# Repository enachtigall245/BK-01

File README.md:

# BK-01
BattleKeeb-01 Prototyping Files

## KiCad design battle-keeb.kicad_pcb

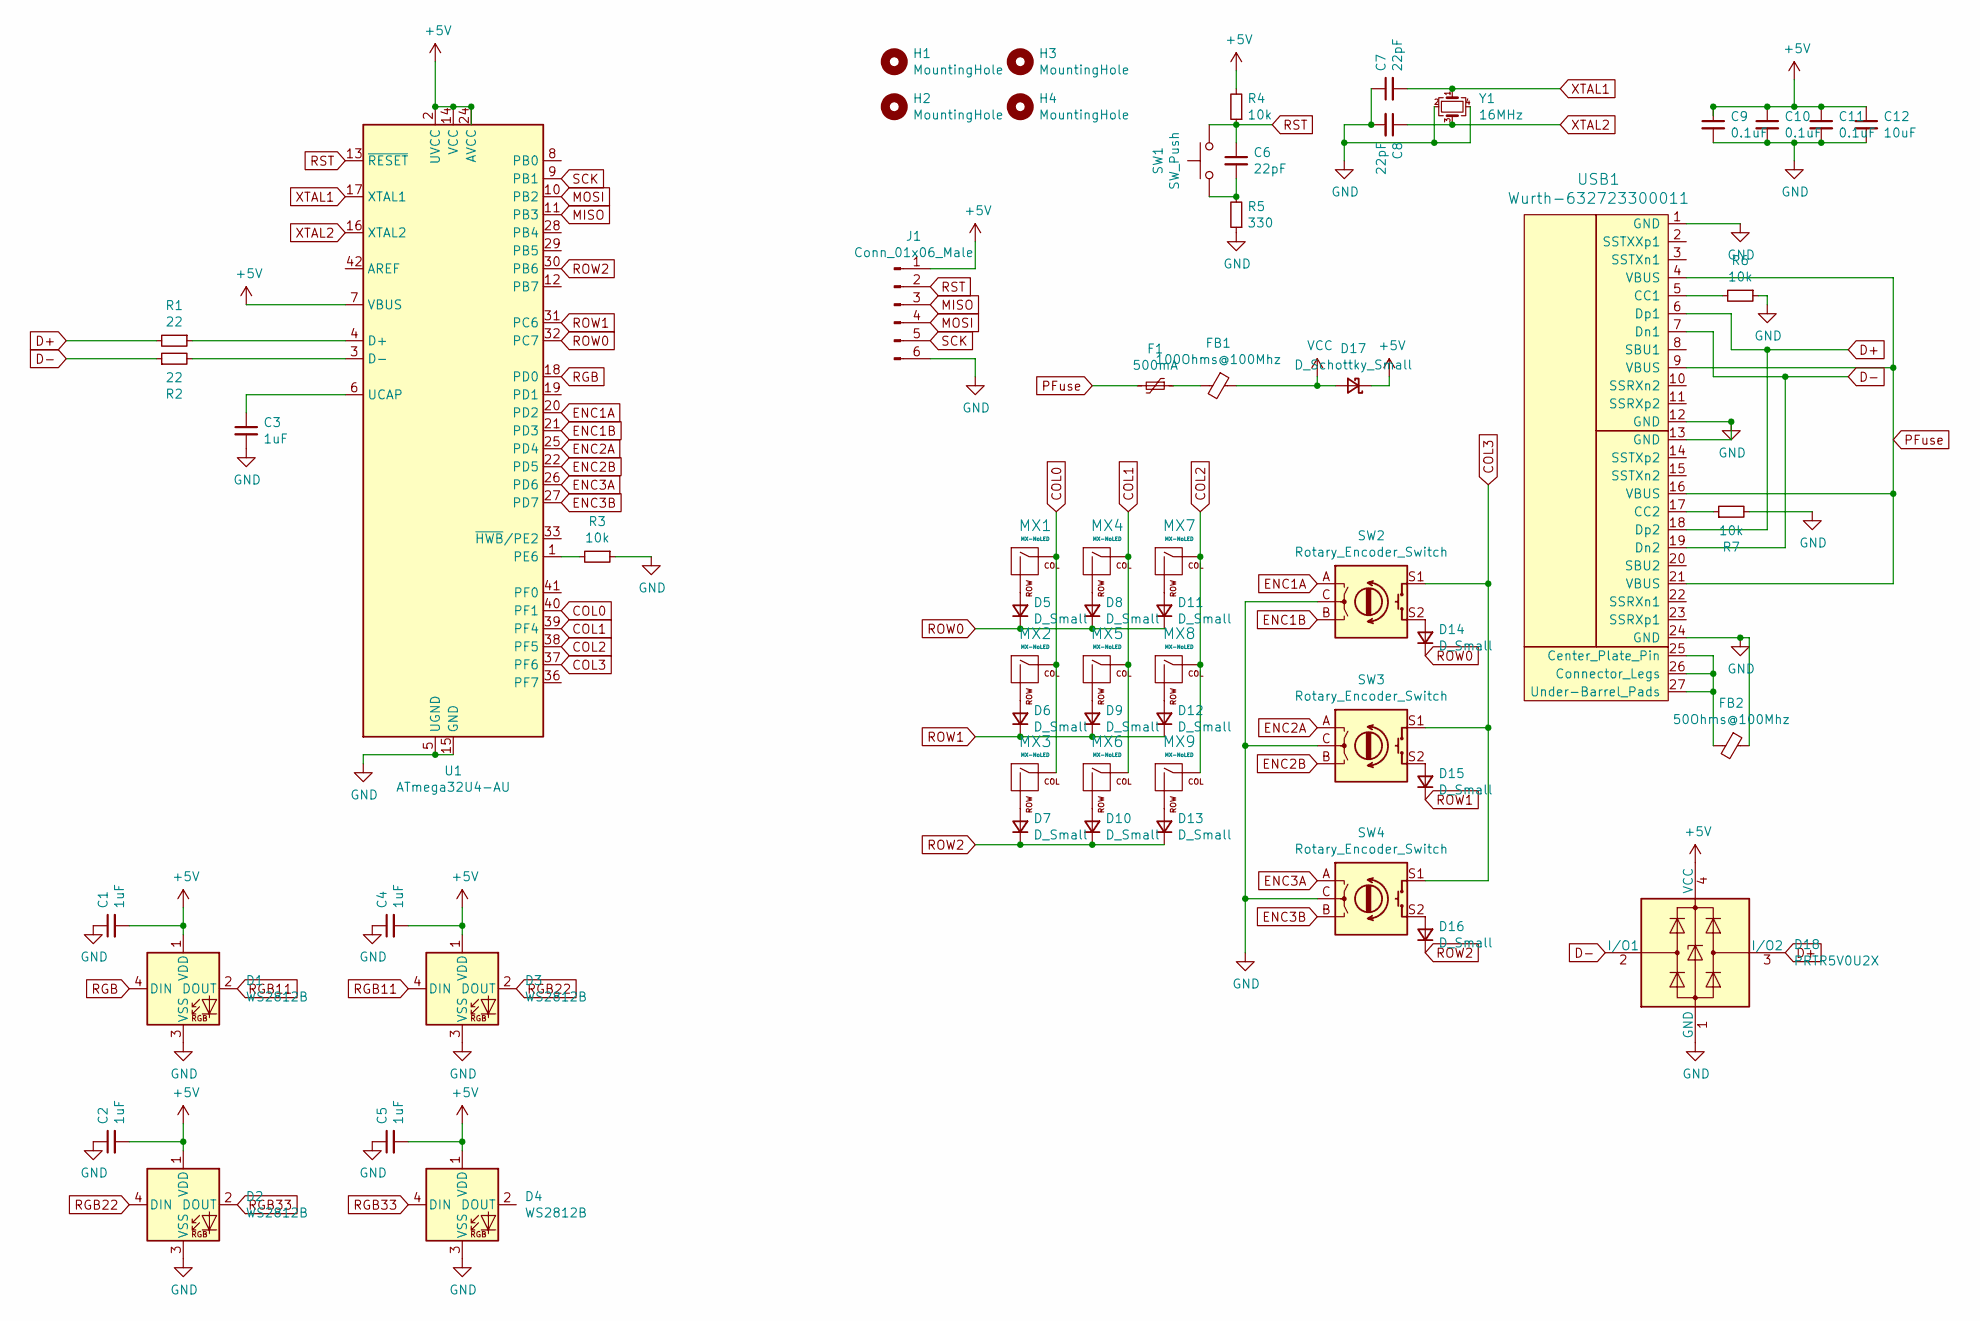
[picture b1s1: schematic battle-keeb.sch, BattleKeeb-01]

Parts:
C1, C2, C3, C4, C5: 1uF; C_0603_1608Metric_Pad1.08x0.95mm_HandSolder
C6, C7, C8: 22pF; C_0603_1608Metric_Pad1.08x0.95mm_HandSolder
C9, C10, C11: 0.1uF; C_0603_1608Metric_Pad1.08x0.95mm_HandSolder
C12: 10uF; C_0603_1608Metric_Pad1.08x0.95mm_HandSolder
D1, D2, D3, D4: WS2812B; LED_WS2812B_PLCC4_5.0x5.0mm_P3.2mm
D5, D6, D7, D8, D9, D10, D11, D12, D13, D14, D15, D16: D_Small; D_SOD-123
D17: D_Schottky_Small; D_SOD-123
D18: PRTR5V0U2X; SOT-143
F1: 500mA; Fuse_1206_3216Metric_Pad1.42x1.75mm_HandSolder
FB1: 100Ohms@100Mhz; R_0603_1608Metric_Pad0.98x0.95mm_HandSolder
FB2: 50Ohms@100Mhz; R_0603_1608Metric_Pad0.98x0.95mm_HandSolder
H1, H2, H3, H4: MountingHole; MountingHole_2.7mm_M2.5_ISO7380_Pad_TopBottom
J1: Conn_01x06_Male; JST_EH_S6B-EH_1x06_P2.50mm_Horizontal
MX1, MX2, MX3, MX4, MX5, MX6, MX7, MX8, MX9: MX-NoLED; MX-1U
R1, R2: 22; R_0603_1608Metric_Pad0.98x0.95mm_HandSolder
R3, R4, R6, R7: 10k; R_0603_1608Metric_Pad0.98x0.95mm_HandSolder
R5: 330; R_0603_1608Metric_Pad0.98x0.95mm_HandSolder
SW1: SW_Push; SKQG-1155865
SW2, SW3, SW4: Rotary_Encoder_Switch; RotaryEncoder_EC11
U1: ATmega32U4-AU; TQFP-44_10x10mm_P0.8mm
USB1: Wurth-632723300011; Wurth-632723300011-HandSoldering
Y1: 16MHz; Crystal_SMD_3225-4Pin_3.2x2.5mm_HandSoldering

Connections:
+5V: C1.2, C2.2, C4.2, C5.2, C9.1, C10.1, C11.1, C12.1, D1.1 (VDD), D2.1 (VDD), D3.1 (VDD), D4.1 (VDD), D17.1 (K), D18.4 (VCC), J1.1, R4.2, U1.2 (UVCC), U1.7 (VBUS), U1.14 (VCC), U1.24 (AVCC), U1.34 (VCC), U1.44 (AVCC)
COL0: MX1.1 (COL), MX2.1 (COL), MX3.1 (COL), U1.40 (PF1)
COL1: MX4.1 (COL), MX5.1 (COL), MX6.1 (COL), U1.39 (PF4)
COL2: MX7.1 (COL), MX8.1 (COL), MX9.1 (COL), U1.38 (PF5)
COL3: SW2.S1, SW3.S1, SW4.S1, U1.37 (PF6)
D+: D18.3 (I/O2), R1.2, USB1.6 (Dp1), USB1.18 (Dp2)
D-: D18.2 (I/O1), R2.1, USB1.7 (Dn1), USB1.19 (Dn2)
ENC1A: SW2.A, U1.20 (PD2)
ENC1B: SW2.B, U1.21 (PD3)
ENC2A: SW3.A, U1.25 (PD4)
ENC2B: SW3.B, U1.22 (PD5)
ENC3A: SW4.A, U1.26 (PD6)
ENC3B: SW4.B, U1.27 (PD7)
GND: C1.1, C2.1, C3.2, C4.1, C5.1, C7.1, C8.2, C9.2, C10.2, C11.2, C12.2, D1.3 (VSS), D2.3 (VSS), D3.3 (VSS), D4.3 (VSS), D18.1 (GND), FB2.1, J1.6, R3.1, R5.1, R6.1, R7.2, SW2.C, SW3.C, SW4.C, U1.5 (UGND), U1.15 (GND), U1.23 (GND), U1.35 (GND), U1.43 (GND), USB1.1 (GND), USB1.12 (GND), USB1.13 (GND), USB1.24 (GND), Y1.2, Y1.4
MISO: J1.3, U1.11 (PB3)
MOSI: J1.4, U1.10 (PB2)
unnamed: C3.1, U1.6 (UCAP)
unnamed: C6.2, R5.2, SW1.1
unnamed: D5.2 (A), MX1.2 (ROW)
unnamed: D6.2 (A), MX2.2 (ROW)
unnamed: D7.2 (A), MX3.2 (ROW)
unnamed: D8.2 (A), MX4.2 (ROW)
unnamed: D9.2 (A), MX5.2 (ROW)
unnamed: D10.2 (A), MX6.2 (ROW)
unnamed: D11.2 (A), MX7.2 (ROW)
unnamed: D12.2 (A), MX8.2 (ROW)
unnamed: D13.2 (A), MX9.2 (ROW)
unnamed: D14.2 (A), SW2.S2
unnamed: D15.2 (A), SW3.S2
unnamed: D16.2 (A), SW4.S2
unnamed: F1.1, FB1.2
unnamed: FB2.2, USB1.25 (Center_Plate_Pin), USB1.26 (Connector_Legs), USB1.27 (Under-Barrel_Pads)
unnamed: R1.1, U1.4 (D+)
unnamed: R2.2, U1.3 (D-)
unnamed: R3.2, U1.1 (PE6)
unnamed: R6.2, USB1.5 (CC1)
unnamed: R7.1, USB1.17 (CC2)
PFuse: F1.2, USB1.4 (VBUS), USB1.9 (VBUS), USB1.16 (VBUS), USB1.21 (VBUS)
RGB: D1.4 (DIN), U1.18 (PD0)
RGB11: D1.2 (DOUT), D3.4 (DIN)
RGB22: D2.4 (DIN), D3.2 (DOUT)
RGB33: D2.2 (DOUT), D4.4 (DIN)
ROW0: D5.1 (K), D8.1 (K), D11.1 (K), D14.1 (K), U1.32 (PC7)
ROW1: D6.1 (K), D9.1 (K), D12.1 (K), D15.1 (K), U1.31 (PC6)
ROW2: D7.1 (K), D10.1 (K), D13.1 (K), D16.1 (K), U1.30 (PB6)
RST: C6.1, J1.2, R4.1, SW1.2, U1.13 (~RESET)
SCK: J1.5, U1.9 (PB1)
VCC: D17.2 (A), FB1.1
XTAL1: C7.2, U1.17 (XTAL1), Y1.1
XTAL2: C8.1, U1.16 (XTAL2), Y1.3

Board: 2 copper layers, 61 parts (13 on the bottom side), 50 nets, no tracks yet.

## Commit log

2021-11-23 Init Project
    Init KiCad Files
2021-11-23 Add Parts 1
    Added parts libraries for switches from https://github.com/ai03-2725/random-keyboard-parts.pretty and https://github.com/daprice/keyswitches.pretty
2021-11-23 Parts Cleanup
    Changed keyswitch library. Added schematic and footprints.
2021-11-23 Schematic Created V1
    Created schematic using parts
2021-11-23 Layout Start
    Layout started. USB-C Footprint needs work.
2021-12-01 Placement and Schematic Update
    Fixed USB-C Connector on schematic and layout - wurth connector for hand assembly. Placed and adjusted components for control, EMI/EMC, USB, JTAG, and other components.
